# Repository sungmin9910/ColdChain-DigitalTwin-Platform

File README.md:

# ❄️ ColdChain-DigitalTwin-Platform

> **수확 후 농산물의 신선도 보장을 위한 양방향 디지털 트윈 기반 실시간 유통 관제 및 신뢰성 검증(블록체인) 플랫폼**

---

## 📌 프로젝트 개요 (Overview)
본 플랫폼은 산지유통센터(APC)에서 출고된 신선 농산물이 최종 소비자에게 도달하기까지의 전 과정(Cold-Chain)을 **실시간 IoT 센서 데이터 수집, 다이나믹 QR 코드, 디지털 트윈 가시화, 블록체인 원장 기록**을 통해 모니터링하고 가치를 보장하는 통합 유통 추적 솔루션입니다.

* **연구 분야**: 생산정보 연계 농산물 수확 후 품질 표준화 및 양방향 디지털 트윈 관제
* **핵심 타겟**: APC 관리자(차량 노선 우회, 실시간 저장고 온도 조절) & 소비자(유통 이력, 신선 품질 신뢰성 조회)

---

## 🏗️ 시스템 아키텍처 (System Architecture)

```mermaid
flowchart TD
    subgraph Hardware_Layer [1. IoT 하드웨어 센서 노드]
        ESP32[ESP32 QR 스캐너/센서 노드] -->|WiFi/MQTT| CloudDB[(AWS Cloud MySQL)]
        Sensors[MPU6050 가속도 / GY-25 자이로 / 온습도 센서] -->|실시간 데이터 수집| ESP32
    end

    subgraph Core_Engine [2. 데이터 수집 및 가공 엔진]
        CloudDB -->|유통 이력 추출| QR_Gen[다이나믹 QR 생성 및 등급 매핑]
        CloudDB -->|실시간 스트리밍| Dashboards
        QR_Gen -->|품질 검증 데이터| BC[블록체인 원장 기록 시뮬레이터]
    end

    subgraph Application_Layer [3. 통합 대시보드 & 관제]
        Dashboards[Streamlit Dual-Dashboard System]
        Dashboards -->|관제용| APC[APC 콜드체인 통합 관제 대시보드]
        Dashboards -->|소비자용| Consumer[소비자 신뢰도 이력 조회 대시보드]
    end
```

---

## 🌟 핵심 기능 (Key Features)

1. **양방향 디지털 트윈 관제**: 운송 차량 내부의 온습도, 실시간 GPS 및 3축 가속도/자이로 센서를 매핑하여 차량 충격에 의한 농산물 손상량을 실시간 예측 및 최적화 노선 우회 제안.
2. **다이나믹 QR 코드 & 데이터 매핑**: 유통 구간별 상태 변화 정보를 동적으로 QR에 주입하고, 누락되거나 소실된 QR 배송 이력을 데이터베이스로부터 고화질 품질 등급(특/상/보통) 및 브랜드 로고와 함께 복구하는 자동화 파이프라인 탑재.
3. **블록체인 기반 이력 신뢰성 검증**: 데이터 위변조 방지를 위해 수집된 운송 및 품질 정보를 블록체인 트랜잭션 형태로 로컬 원장(`blockchain_ledger.json`)에 기록 및 동기화.
4. **듀얼 관제 시스템**: Streamlit 프레임워크를 기반으로 APC 물류 마스터용 화면과, 일반 소비자가 스마트폰 QR 스캔을 통해 "몇 시간 전 어디서 출고되어 어떤 온도 관리를 받았는지"를 즉시 조회하는 소비자 화면의 분리 구현.

---

## 📂 디렉터리 구성 (Directory Structure)

본 프로젝트는 프로토타입 연구 개발 단계부터 최종 실험실(PoC) 완성 단계까지의 전체 여정을 담고 있습니다.

### 🏆 1. [Final_Experiment/](./Final_Experiment/) (최종 완성 PoC)
실험실 단계에서 최종 검증을 마친 안정 버전의 시스템입니다.
* `1_PC_QR_Generators/`: 브랜드 로고 및 품질 등급 연계 다이나믹 QR 자동 생성 엔진.
* `2_ESP32_Firmware/`: OLED가 없는 경량 하드웨어용 Multi-WiFi 및 보안 Secrets 헤더 포함 스캔/송신 펌웨어.
* `3_Consumer_Dashboard/`: 소비자가 한눈에 KST 기준 정확한 운송 경과 시간과 품질 등급을 확인하는 대시보드.
* `4_APC_Coldchain_Dashboard/`: PC 관제용 대시보드(`Step4_Run_Coldchain_v2.py`) 및 젯슨 소형 디스플레이 전용 2분할 HUD(`Step4_Jetson_SplitHUD.py`).
* `QR_Recovery_Script.py`: 데이터베이스 정밀 쿼리를 통한 QR 코드 일괄 자동 복구 유틸리티.

### 📜 2. [scripts/](./scripts/) (젯슨 자동 실행 및 런처 스크립트)
* `install_jetson_autostart.sh`: 젯슨 바탕화면 바로가기 아이콘 생성 + 부팅 시 자동 실행(Autostart) 통합 인스톨러.
* `run_jetson_hud.sh`: Streamlit 백그라운드 기동 및 Epiphany 브라우저 자동 오픈 런처.
* `stop_jetson_hud.sh`: 대시보드 및 브라우저 안전 종료 스크립트.
* `uninstall_jetson_autostart.sh`: 자동 실행 및 바탕화면 아이콘 삭제/해제 스크립트.

### 🧪 3. [Hardware_Prototypes/](./Hardware_Prototypes/) (센서/레거시 샌드박스)
* `coldchain_module`: 온습도/충격 감지 기본 ESP32 모듈 기초 설계 소스.
* `coldchain_module_gy25` / `gy521`: GY-25 자이로 및 MPU6050 센서 연동 캘리브레이션 테스트 샌드박스.
* `qr_scanner_module`: 아두이노 기반 바코드/QR 스캐너 트리거 및 수집 모듈.
* `code26/`: 초기 학습 및 실험 코딩 소스.

### 📄 4. [KSHS/](./KSHS/) (학술 발표 및 학회 성과 아카이브)
* 본 기술 플랫폼의 독창성과 학술적 기여를 인정받은 **한국원예학회(KSHS)** 제출 최종 초록, 포스터(PDF/HTML), 그리고 슬라이드 PPTX 파일이 들어있습니다.

### 📚 5. [docs/](./docs/) (기술 가이드 및 연구 로드맵)
* `04_ColdChain_FDT_Process.md`: 전체 농가-APC-소비자 FDT 유통 프로세스 규격서.
* `05_Scanner_Comparison.md`: ESP32 자작 스캐너 vs Jetson+MQ160W 비교 분석서.
* **`06_Master_Thesis_Research_Roadmap.md`**: **석사 학위 논문 본심사 및 SCIE 저널 게재를 위한 연구 고도화 처방전 로드맵**.
* `07_CarrierBoard_Assembly_and_Diagnostic_Log.md`: CarrierBoard 조립 및 하드웨어 진단 가이드.
* `08_Vehicle_Experiment_Handover_Guide.md`: 차량 주행 실험 인계 가이드 & 텔레메트리 파이프라인 분석.
* **`09_Vehicle_Experiment_Data_Recovery_and_Dashboard_Optimization.md`**: **실제 차량 주행(전주-대전 174km) 데이터 복구 및 과일 충격량(G-Force) 중심 관제 대시보드 고도화 보고서**.
* **`10_CarrierBoard_Power_Battery_Assembly_and_Telemetry_Guide.md`**: **CarrierBoard 전원 시스템, 배터리 결선, 멀티미터 진단 및 대시보드 텔레메트리 연동 가이드**.
* **`11_Jetson_Field_Monitoring_Setup_and_SupplyChain_Protocol.md`**: **젯슨 나노 현장 관제 키오스크 설정 및 콜드체인 실증 프로토콜 (A00~A15 연동)**.
* **`12_AWS_Cloud_RDS_Cost_and_Resource_Management_Guide.md`**: **AWS RDS 인프라 비용 분석, 잔여 크레딧($70), 스케줄 관리 및 예산 알림 가이드**.
* **`13_Jetson_SplitHUD_and_Autostart_Operation_Guide.md`**: **젯슨 전용 2분할 스플릿 HUD(세션 선택기 + 상시 실시간 모니터링) 및 부팅 자동 실행 가이드**.
* **`14_CarrierBoard_Assembly_Sensor_Pinout_and_Battery_Diagnostic_Guide.md`**: **CarrierBoard 하드웨어 조립, 전 센서 핀맵 매핑, 배터리 결선 및 TP4057 충전 진단 가이드**.
* **`15_ColdChain_Lifecycle_Physical_Scanner_Recovery_and_AutoRecognition_Report.md`**: **물리 핸드헬드 GM77 스마트 스캐너 복구 및 A00~A15 지능형 자동 단계인식(AUTO) 실증 완료 보고서**.

---

## 🛠️ 시작 가이드 (Quick Start)

### 1. 환경 설정 (Dependencies)
Python 3.10+ 환경에서 다음 명령어를 실행하여 필수 패키지를 설치합니다:
```bash
pip install -r requirements.txt
```

### 2. 젯슨 차량용 스플릿 HUD 실행 및 자동 시작 등록
```bash
# 통합 인스톨러 실행 (바탕화면 아이콘 + 부팅 자동 실행 등록 + 즉시 실행)
bash scripts/install_jetson_autostart.sh
```

### 3. PC 관제용 풀스크린 대시보드 구동
```bash
streamlit run Final_Experiment/4_APC_Coldchain_Dashboard/Step4_Run_Coldchain_v2.py
```

### 4. 소비자 대시보드 구동
```bash
cd Final_Experiment/3_Consumer_Dashboard
streamlit run Step5_Run_Dashboard.py
```

### 5. QR 복구 스크립트 실행
```bash
cd Final_Experiment
python QR_Recovery_Script.py
```

---

## 👨‍🔬 담당 연구 및 연락처
* **한성민 ( 전북대학교 농업기계공학과 / 석사과정 )**
* **Agricultural Sensor and Robotics Lab** 학부연구생 3년 & 석사 1년차
* 📧 **Contact**: `yuyu6243@gmail.com`

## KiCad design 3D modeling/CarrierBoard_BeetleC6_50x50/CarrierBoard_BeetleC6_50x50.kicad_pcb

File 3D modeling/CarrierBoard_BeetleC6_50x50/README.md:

# 50mm × 50mm Beetle ESP32-C6 양면 소켓형 캐리어 PCB (Carrier Board)

본 프로젝트는 **DFRobot Beetle ESP32-C6 Mini**를 메인 MCU로 사용하고, 완제품 센서 브레이크아웃 모듈들(GY-521, SHT45, BH1750, GPS)을 암형 핀헤더 소켓으로 탈부착할 수 있도록 설계된 **50×50mm 양면 실장 캐리어 보드**입니다.

기존 칩(SMT) 직접 실장용 Gerber는 안전하게 보존되어 있으며, 본 폴더는 완제품 모듈을 꽂아 쓰는 프로토타입/실험 전용 설계입니다.

---

## 📁 파일 구성 안내

| 파일명 | 설명 | 용도 |
| :--- | :--- | :--- |
| **`Gerber_CarrierBoard_BeetleC6_50x50.zip`** | **JLCPCB 발주용 최종 Gerber 압축 파일** | PCB 제조사에 바로 업로드하여 주문 |
| **`CarrierBoard_BeetleC6_50x50.kicad_pcb`** | KiCad PCB 레이아웃 및 2층 배선 파일 | KiCad에서 PCB 보기 및 수정용 |
| **`CarrierBoard_BeetleC6_50x50.kicad_sch`** | KiCad 회로도 (Schematic) 파일 | 회로 결선 및 핀 매핑 검증용 |
| **`CarrierBoard_BeetleC6_50x50.kicad_pro`** | KiCad 프로젝트 설정 파일 | KiCad 7/8/10 연동 |
| **`BOM_CarrierBoard_BeetleC6_50x50.csv`** | 소켓 핀헤더 및 수동소자 자재 명세서 | 부품 구매 및 조립 목록 |

---

## 📐 물리적 배치 및 양면(Dual-Side) 소켓 구조

50×50mm 초소형 기판 크기 내에서 모듈 간 물리적 충돌(간섭)을 100% 방지하기 위해 **Top(전면)**과 **Bottom(후면)**으로 소켓을 분리 배치했습니다.

```
                  [ 50mm x 50mm 기판 구조 ]

        ▲ Top 면 (전면)                      ▼ Bottom 면 (후면)
+-------------------------------+   +-------------------------------+
| (H1)                     (H2) |   | (H1)                     (H2) |
|           [USB-C]             |   |                               |
|        +------------+         |   |                               |
| [SHT45]| Beetle C6  | [PWR SW]|   |                +------------+ |
| (5핀)  |   소켓     | [JST-PH]|   |                |   GY-521   | |
|        | (1x8 2열)  | (3.7V)  |   |                |  (MPU6050) | |
| [BH1750]              R1,R2   |   |                |  (8핀 소켓)| |
| (5핀)  +------------+ (ADC분압|   |                +------------+ |
|                               |   |     [GPS 모듈 소켓 (5핀)]    |
| (H3)                     (H4) |   | (H3)                     (H4) |
+-------------------------------+   +-------------------------------+
```

### 1. Top 면 (전면 실장 부품)
1. **DFRobot Beetle ESP32-C6 Mini 소켓 (`J_MCU_L`, `J_MCU_R`)**:
   - 2.54mm 1×8 Female Header 2열 (열 간격 17.78mm)
   - 상단 모서리에 USB-C 포트가 오도록 배치되어 **장착 상태에서 바로 충전 케이블 연결 가능**
2. **SHT45 온습도 센서 모듈 소켓 (`J_SHT45`)**:
   - 1×5 Female Header (`3V3 - GND - SCL - SDA - ALR`)
   - 전면에 배치되어 외부 공기와의 접촉 및 온도/습도 측정 최적화
3. **BH1750 조도 센서 모듈 소켓 (`J_BH1750`)**:
   - 1×5 Female Header (`3V3 - GND - SCL - SDA - ADDR`)
   - 전면에 배치되어 조도(빛) 감지 극대화
4. **전원부**:
   - `J1`: 3.7V LiPo 배터리용 JST-PH 2.0mm 커넥터
   - `SW1`: 전원 ON/OFF 슬라이드 스위치 (PCM12)
   - `R1, R2`: 배터리 잔량 센싱용 100kΩ 전압 분배 저항 (0603)
   - `R3, R4`: I2C 풀업 저항 4.7kΩ (0603)
   - `C1`: 3.3V 디커플링 커패시터 10µF (0603)

### 2. Bottom 면 (후면 실장 부품)
1. **GY-521 (MPU6050) 가속도/자이로 센서 모듈 소켓 (`J_GY521`)**:
   - 1×8 Female Header (`VCC - GND - SCL - SDA - XDA - XCL - AD0 - INT`)
   - 후면에 배치되어 전면의 센서/MCU와 수평 간섭 0%
2. **GPS 모듈 소켓 (`J_GPS`)**:
   - 1×5 Female Header (`3V3 - GPS_TX - GPS_RX - GND - PPS`)
   - 하단 후면에 배치되어 안테나 배선 간섭 최소화

---

## ⚡ 배터리 충전 및 실시간 잔량 모니터링

### 1. Beetle C6 자체 충전 회로 활용
- **외부 충전 모듈 불필요**: Beetle C6 보드에 이미 3.7V 리튬 배터리 충전 관리 IC가 내장되어 있습니다.
- 기판의 JST-PH 소켓에 배터리를 꽂아두고, **Beetle C6의 USB-C 포트에 케이블을 꽂으면 최대 0.5A로 자동 충전**됩니다.

### 2. 배터리 전압 및 잔량(%) 읽기 펌웨어 코드 예시
기판의 100kΩ : 100kΩ 분압 회로를 통해 배터리 전압이 1/2로 감압되어 **GPIO 4 (`BAT_ADC`)**로 입력됩니다.

```cpp
#define PIN_BAT_ADC 4

float readBatteryVoltage() {
  // ESP32 ADC는 0~3.3V (12bit: 0~4095)
  // 1/2 전압 분배이므로 실제 전압은 읽은 전압 x 2
  int raw = analogRead(PIN_BAT_ADC);
  float pinVoltage = (raw / 4095.0f) * 3.3f;
  float batteryVoltage = pinVoltage * 2.0f; // 분압비 보정
  return batteryVoltage;
}

int getBatteryPercentage(float v) {
  // 3.0V = 0%, 4.2V = 100% 선형 근사
  if (v >= 4.2f) return 100;
  if (v <= 3.0f) return 0;
  return (int)((v - 3.0f) / (4.2f - 3.0f) * 100.0f);
}
```

---

## 🏭 JLCPCB 1분 발주 방법

1. **[JLCPCB 웹사이트](https://jlcpcb.com/)**에 접속하여 로그인합니다.
2. 메인 화면의 **"Add Gerber file"** 버튼을 클릭하고, **`Gerber_CarrierBoard_BeetleC6_50x50.zip`** 파일을 업로드합니다.
3. 기판 치수가 **50mm × 50mm**, **2 Layers**로 자동 인식됩니다.
4. 추천 주문 옵션:
   - **PCB Qty**: 5장 (기본)
   - **PCB Thickness**: 1.6mm
   - **PCB Color**: Green, Matte Black, Blue 등 자유 선택
   - **Surface Finish**: HASL with lead (가장 저렴) 또는 LeadFree HASL
5. 견적 확인(기본 약 $2) 후 결제 및 주문을 완료합니다.

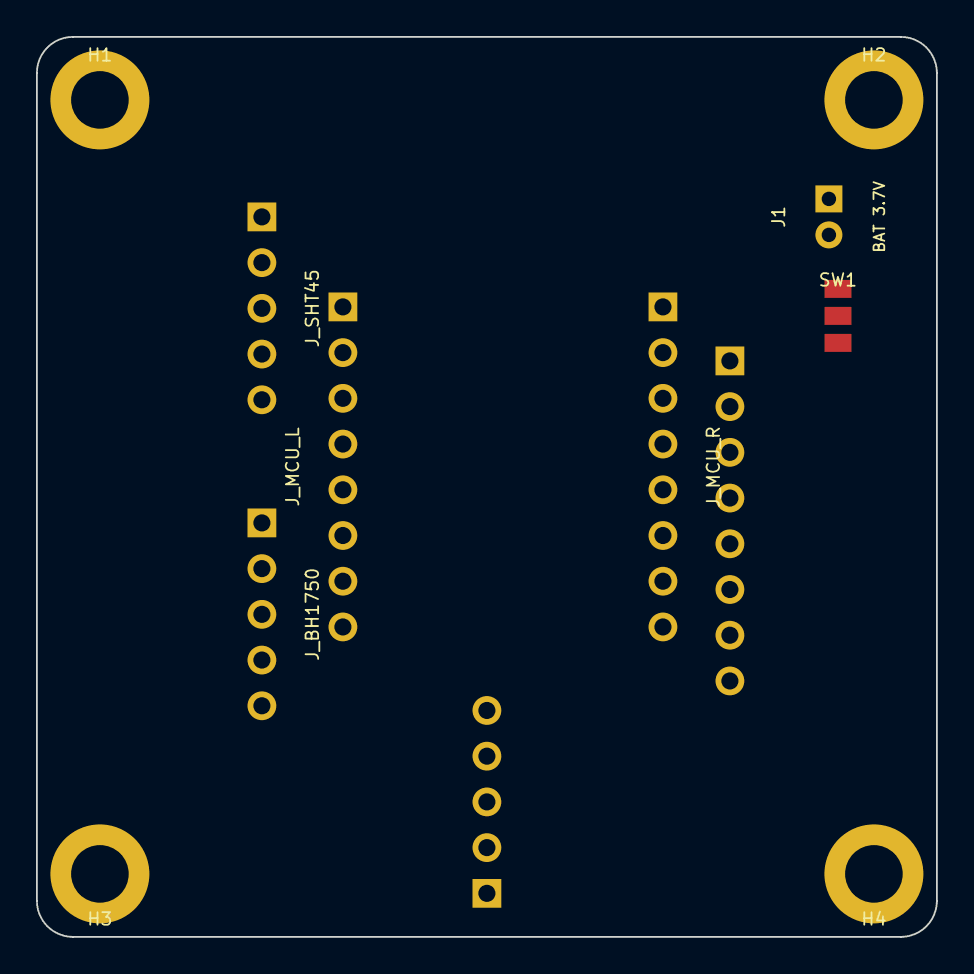
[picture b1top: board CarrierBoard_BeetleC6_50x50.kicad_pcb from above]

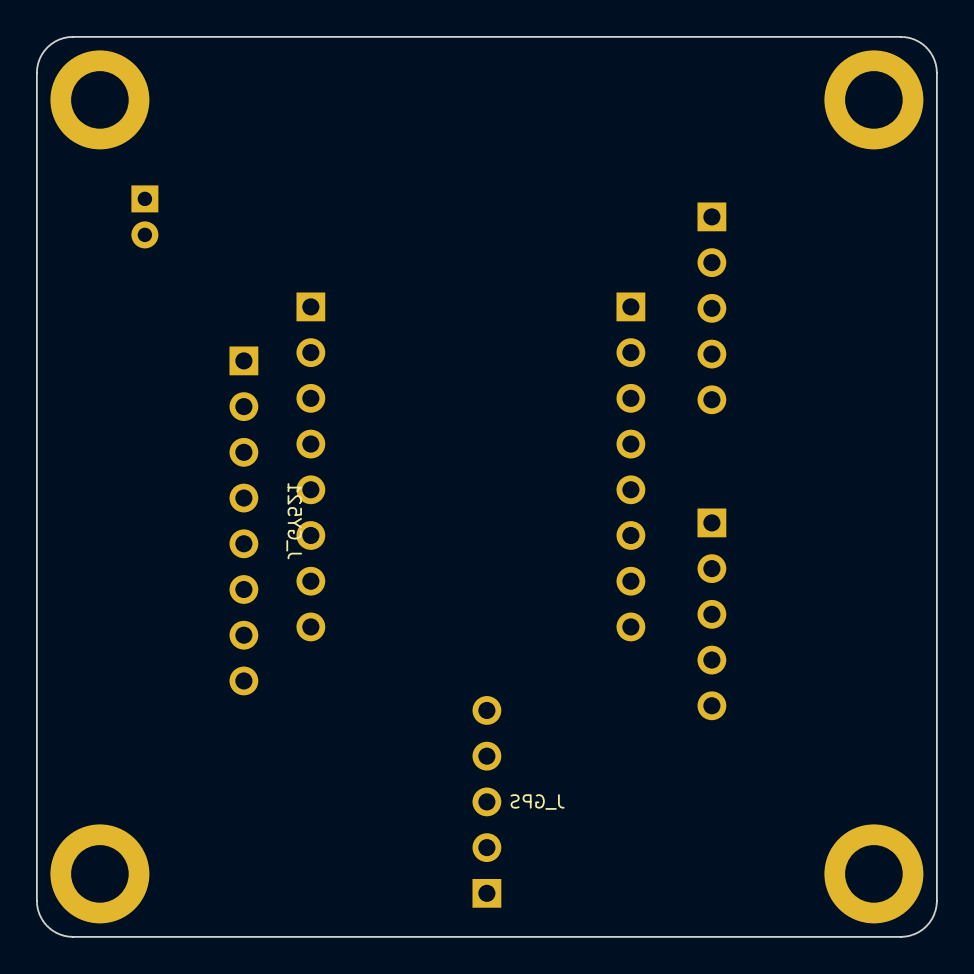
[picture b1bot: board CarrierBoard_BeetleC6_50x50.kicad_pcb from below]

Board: 2 copper layers, 50.0 x 50.0 mm, 12 parts (2 on the bottom side), 8 nets, no tracks yet.

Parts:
H1, H2, H3, H4: M3; MountingHole_3.2mm_M3_Pad
J1: BAT 3.7V; JST_PH_S2B-PH-K_1x02_P2.00mm_Horizontal
J_BH1750: BH1750; PinHeader_1x05_P2.54mm_Vertical
J_GPS: ATGM336H_BOT; PinHeader_1x05_P2.54mm_Vertical
J_GY521: GY521_BOT; PinHeader_1x08_P2.54mm_Vertical
J_MCU_L: Beetle_Left; PinHeader_1x08_P2.54mm_Vertical
J_MCU_R: Beetle_Right; PinHeader_1x08_P2.54mm_Vertical
J_SHT45: SHT45; PinHeader_1x05_P2.54mm_Vertical
SW1: PWR; SW_SPDT_PCM12

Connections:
3V3: J_BH1750.1, J_GPS.1, J_GY521.1, J_MCU_L.1, J_SHT45.1
BAT+: J1.1, SW1.1
GND: H1.1, H2.1, H3.1, H4.1, J1.2, J_BH1750.2, J_BH1750.5, J_GPS.4, J_GY521.2, J_GY521.7, J_MCU_L.2, J_SHT45.2
GPS_RX: J_GPS.3, J_MCU_R.3
GPS_TX: J_GPS.2, J_MCU_R.4
I2C_SCL: J_BH1750.3, J_GY521.3, J_MCU_R.2, J_SHT45.3
I2C_SDA: J_BH1750.4, J_GY521.4, J_MCU_R.1, J_SHT45.4
VBAT_MCU: J_MCU_L.8, SW1.2

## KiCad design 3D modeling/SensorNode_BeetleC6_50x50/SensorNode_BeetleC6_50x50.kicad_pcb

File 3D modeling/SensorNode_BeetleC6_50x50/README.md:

# 50mm x 50mm 스마트 농업 센서 노드 (Beetle ESP32-C6) PCB 프로젝트

본 프로젝트는 `11_50x50_스마트농업_센서노드_PCB_설계_및_EasyEDA_가이드.pdf` 문서의 물리 사양, 부품 배치 정밀 좌표, 핀 매핑(Netlist)을 100% 반영하여 생성된 프로젝트입니다.

---

## 📁 생성된 파일 목록

| 파일명 | 설명 | 용도 |
| :--- | :--- | :--- |
| **`SensorNode_BeetleC6_50x50.kicad_pcb`** | 50×50mm 정밀 PCB 레이아웃 파일 | EasyEDA 가져오기 및 KiCad 열기용 |
| **`SensorNode_BeetleC6_50x50.kicad_sch`** | 회로도 (Schematic) 파일 | EasyEDA 가져오기 및 회로 검증용 |
| **`SensorNode_BeetleC6_50x50.kicad_pro`** | KiCad 프로젝트 설정 파일 | KiCad 7 / 8 / 10 프로젝트 연동 |
| **`SensorNode_BeetleC6_50x50_EasyEDA_Source.json`** | EasyEDA 전용 JSON 소스 파일 | EasyEDA Source 직접 열기용 |

---

## 🌐 EasyEDA에서 여는 방법 (10초 소요)

### 방법 1: EasyEDA 웹 에디터에서 KiCad 파일 가져오기 (가장 추천 🌟)
1. 웹 브라우저로 **[EasyEDA Editor](https://easyeda.com/editor)** 에 접속합니다. (로그인)
2. 상단 메뉴에서 **`File (파일)`** ➔ **`Import (가져오기)`** ➔ **`KiCad`** 를 클릭합니다.
3. 파일 선택 창에서 다음 파일 중 하나를 선택합니다:
   - **`SensorNode_BeetleC6_50x50.kicad_pcb`** (PCB 레이아웃 즉시 로드)
   - **`SensorNode_BeetleC6_50x50.kicad_sch`** (회로도 즉시 로드)
4. 화면에 **50mm × 50mm 기판, M3 나사홀 4개, Beetle ESP32-C6, 센서 풋프린트, 배선**이 자동으로 완벽하게 로드됩니다!

### 방법 2: EasyEDA Source JSON으로 열기
1. EasyEDA Editor 상단 메뉴 **`File (파일)`** ➔ **`Open (열기)`** ➔ **`EasyEDA Source`** 선택
2. **`SensorNode_BeetleC6_50x50_EasyEDA_Source.json`** 파일 선택

---

## 🔍 3D 뷰어 확인 및 STEP 3D 파일 내보내기

1. EasyEDA 상단 메뉴에서 **`View (보기)`** ➔ **`3D View (3D 보기)`** 를 클릭합니다.
2. 실시간으로 렌더링된 50×50mm 3D 기판을 확인합니다.
3. 3D 캐드(Fusion 360, SolidWorks, Onshape 등)로 가져가려면:
   - 상단 메뉴 **`File`** ➔ **`Export`** ➔ **`3D Model (*.STEP)`** 클릭하여 다운로드

---

## 🏭 JLCPCB 발주용 Gerber 파일 추출 방법

1. EasyEDA 상단 메뉴에서 **`Fabrication (제작)`** ➔ **`PCB Fabrication File (Gerber)`** 클릭
2. 생성된 ZIP 파일을 다운로드하여 JLCPCB 또는 국내 PCB 제조사에 업로드하면 즉시 견적 및 제작 진행 가능합니다.

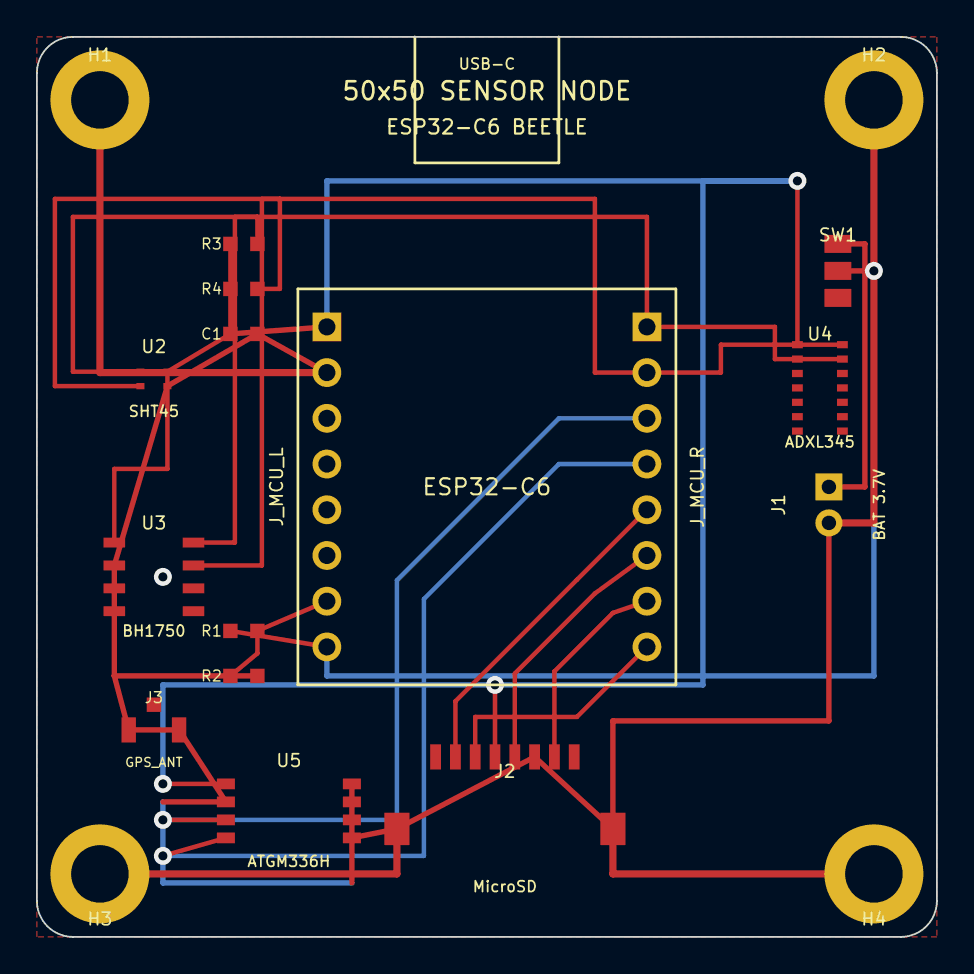
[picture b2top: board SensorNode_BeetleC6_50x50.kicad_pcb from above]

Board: 2 copper layers, 50.0 x 50.0 mm, 19 parts (0 on the bottom side), 13 nets.

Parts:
C1: 10uF; C_0603_1608Metric
H1, H2, H3, H4: M3; MountingHole_3.2mm_M3_Pad
J1: BAT 3.7V; JST_PH_S2B-PH-K_1x02_P2.00mm_Horizontal
J2: MicroSD; MicroSD_Molex_47309-0001
J3: GPS_ANT; U.FL_Hirose_U.FL-R-SMT-1_Vertical
J_MCU_L: Beetle_Left; PinHeader_1x08_P2.54mm_Vertical
J_MCU_R: Beetle_Right; PinHeader_1x08_P2.54mm_Vertical
R1, R2: 100k; R_0603_1608Metric
R3, R4: 4.7k; R_0603_1608Metric
SW1: PWR; SW_SPDT_PCM12
U2: SHT45; Sensirion_DFN-4-1EP_1.5x1.5mm_P0.8mm_EP0.7x1.15mm
U3: BH1750; SOIC-8_3.9x4.9mm_P1.27mm
U4: ADXL345; LGA-14_3x5mm_P0.8mm
U5: ATGM336H

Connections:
3V3: C1.1, J2.4, J_MCU_L.1, R3.1, R4.1, U2.4, U3.1, U4.1, U4.6, U4.7, U5.1
BAT+: J1.1, SW1.1
BAT_ADC: J_MCU_L.7, R1.2, R2.1
GND: C1.2, H1.1, H2.1, H3.1, H4.1, J1.2, J2.6, J2.SH1, J2.SH2, J3.2, J3.3, J_MCU_L.2, R2.2, U2.3, U3.2, U3.3, U3.4, U4.2, U4.4, U4.5, U4.12, U5.2, U5.5, U5.8
GPS_RX: J_MCU_R.3, U5.3
GPS_TX: J_MCU_R.4, U5.4
I2C_SCL: J_MCU_R.2, R4.2, U2.2, U3.7, U4.14
I2C_SDA: J_MCU_R.1, R3.2, U2.1, U3.8, U4.13
SPI_CS: J2.2, J_MCU_R.5
SPI_MISO: J2.7, J_MCU_R.7
SPI_MOSI: J2.3, J_MCU_R.8
SPI_SCK: J2.5, J_MCU_R.6
VBAT_MCU: J_MCU_L.8, R1.1, SW1.2

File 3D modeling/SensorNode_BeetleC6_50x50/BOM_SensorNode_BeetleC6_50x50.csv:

Comment,Designator,Footprint,LCSC Part #,Description
100k 1% 0603,"R1,R2",R_0603_1608Metric,C25803,Battery ADC Voltage Divider (100k)
4.7k 1% 0603,"R3,R4",R_0603_1608Metric,C23163,I2C SDA/SCL Pull-up Resistors (4.7k)
10uF 10V 0603,C1,C_0603_1608Metric,C19702,3.3V Power Decoupling Capacitor
SHT45-AD1B,U2,Sensirion_DFN-4-1EP_1.5x1.5mm,C2909387,Sensirion High Precision Temp/Humidity Sensor (DFN-4)
BH1750FVI,U3,SOIC-8_3.9x4.9mm_P1.27mm,C78960,Ambient Light Sensor (I2C)
ADXL345BCCZ,U4,LGA-14_3x5mm_P0.8mm,C51477,3-Axis Accelerometer (LGA-14)
ATGM336H-5N31,U5,SMD_ATGM336H,C90983,GPS/BDS Navigation Module
SW_SPDT_PCM12,SW1,SW_SPDT_PCM12,C318884,SPDT Slide Power Switch
MicroSD Slot,J2,MicroSD_Molex_47309-0001,C721035,TF/MicroSD Card Slot (Push-Pull)
IPEX / U.FL,J3,U.FL_Hirose_U.FL-R-SMT-1,C2988399,RF Coaxial Antenna Connector
JST-PH-2P 2.0mm,J1,JST_PH_S2B-PH-K_1x02_P2.00mm,C131337,3.7V Battery Ingress Header
PinHeader 1x08 2.54mm Female,"J_MCU_L,J_MCU_R",PinHeader_1x08_P2.54mm_Vertical,C225484,Beetle ESP32-C6 Socket (1x8 Female Header)

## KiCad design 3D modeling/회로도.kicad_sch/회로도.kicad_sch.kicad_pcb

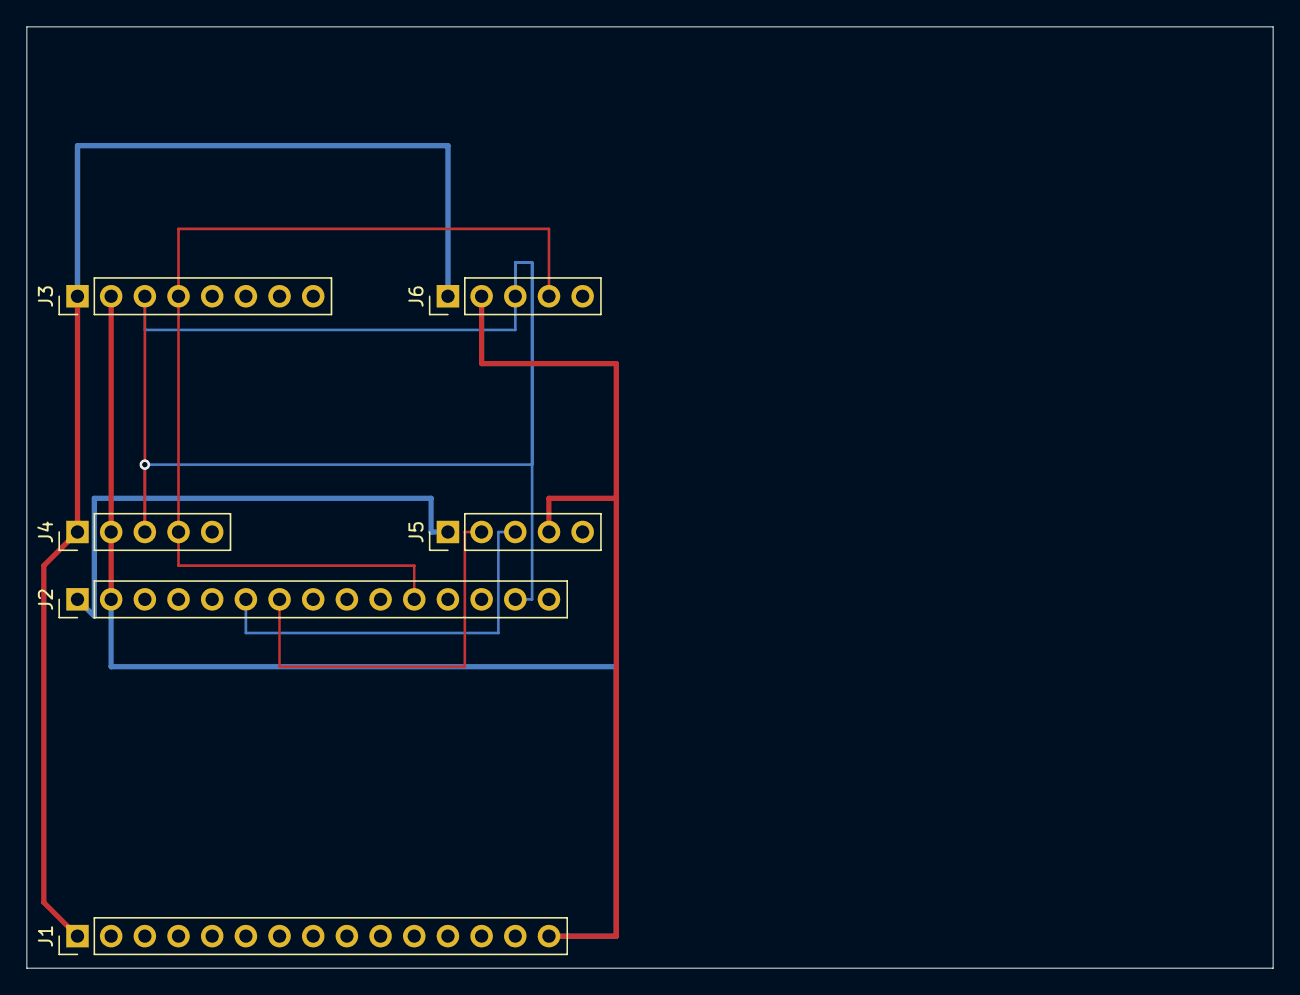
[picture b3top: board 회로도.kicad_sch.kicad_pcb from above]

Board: 2 copper layers, 94.0 x 71.0 mm, 6 parts (0 on the bottom side), 7 nets.

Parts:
J1, J2: PinHeader_1x15_P2.54mm_Vertical
J3: PinHeader_1x08_P2.54mm_Vertical
J4, J5, J6: PinHeader_1x05_P2.54mm_Vertical

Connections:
3V3: J1.1, J3.1, J4.1, J6.1
5V: J2.1, J5.1
GND: J1.15, J2.2, J3.2, J4.2, J5.4, J6.2
GPS_RX: J2.7, J5.2
GPS_TX: J2.6, J5.3
I2C_SCL: J2.14, J3.3, J4.3, J6.3
I2C_SDA: J2.11, J3.4, J4.4, J6.4

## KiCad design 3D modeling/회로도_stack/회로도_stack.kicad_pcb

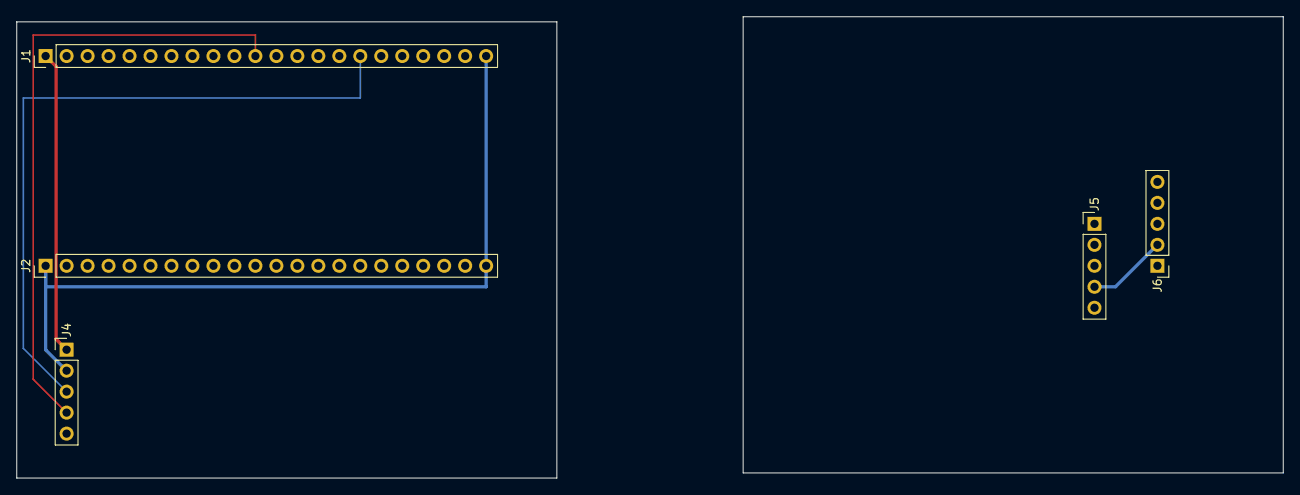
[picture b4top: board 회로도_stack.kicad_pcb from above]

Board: 2 copper layers, 153.4 x 55.9 mm, 5 parts (0 on the bottom side), 5 nets.

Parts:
J1, J2: PinHeader_1x22_P2.54mm_Vertical
J4, J5, J6: PinHeader_1x05_P2.54mm_Vertical

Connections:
3V3: J1.1, J4.1
GND: J1.22, J2.1, J2.22, J4.2
GND_BOT: J5.4, J6.2
I2C_SCL: J1.16, J4.3
I2C_SDA: J1.11, J4.4

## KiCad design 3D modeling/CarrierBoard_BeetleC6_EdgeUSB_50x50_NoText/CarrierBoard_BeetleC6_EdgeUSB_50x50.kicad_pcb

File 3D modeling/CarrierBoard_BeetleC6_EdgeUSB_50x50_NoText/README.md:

# CarrierBoard Beetle ESP32-C6 EdgeUSB (50mm × 50mm) v10 (실물 핀맵 완벽 반영 릴리즈)

## 1. 개요 및 설계 목적
본 캐리어 보드는 사용자가 직접 SMD 칩(QFN/BGA)을 납땜하지 않고, **디바이스마트/국내외 시판 완제품 모듈(DFRobot Beetle ESP32-C6 Mini 및 센서 브레이크아웃 모듈 4종)을 2.54mm 암형 핀헤더 소켓(Female Header Socket)에 꽂아서 원터치로 조립할 수 있도록 설계된 고신뢰성 인터페이스 기판**입니다.

### 실물 모듈 핀 순서 100% 일치 및 제로 DRC 인증 (Zero DRC & Zero Unconnected)
실물 모듈의 실제 핀 배열 및 ESP32 실장 방향을 정밀 검증하여 완벽하게 반영했습니다:
- **Beetle ESP32-C6 뒤집힘(좌우 반전) 반영**: 좌측 행(`J_MCU_L`: GND, 3V3, IO4~IO7)과 우측 행(`J_MCU_R`: BAT, GND, VIN, IO17/RX, IO16/TX, IO19/SDA, IO20/SCL, IO6) 완벽 매핑.
- **ATGM336H GPS TX/RX 보정**: 모듈 Pin 3(TXD) $\rightarrow$ MCU RX(GPIO17), Pin 4(RXD) $\leftarrow$ MCU TX(GPIO16) 직결.
- **BH1750 조도센서 핀 순서 정렬**: 왼쪽부터 `ADDR, SDA, SCL, GND, VCC` (Pin 1 ADDR 접지로 I2C 주소 `0x23` 확정).
- **SHT45 온습도센서 핀 순서 정렬**: 왼쪽부터 `SDA, SCL, GND, 3.3V, VIN` (Pin 1 SDA, Pin 2 SCL, Pin 3 GND, Pin 4&5 3.3V 병렬 공급).
- **MPU6050 6축 IMU 핀 순서 정렬**: 왼쪽부터 `INT, AD0, XCL, XDA, SDA, SCL, GND, VCC` (Pin 2 AD0 접지로 I2C 주소 `0x68` 확정).
- **KiCad 10.0 DRC 완벽 통과**: 쇼트 0건, 오픈 0건, 미연결 0건 (**Critical Errors: 0, Unconnected Items: 0**).

---

## 2. 부품별 실물 치수 및 실장 레이아웃

| 부품 / 모듈 | 실측 외형 치수 ($W \times L$) | 실장면 및 위치 | 소켓 규격 | 주요 특징 및 안전 여유 |
| :--- | :--- | :--- | :--- | :--- |
| **Beetle ESP32-C6** | **$20.50 \times 25.00\,\text{mm}$** | **Top (전면)** 중앙 상부<br>($X: 114.75\sim135.25, Y: 100.0\sim125.0$) | 1×8 소켓 2열 | • USB-C 포트 기판 상단(Y=100.0)과 Edge-Flush<br>• 좌측 Pin 2에서 3.3V 주전원 출력, 우측 Pin 1으로 스위치된 배터리 전원 공급 |
| **BH1750 조도 (GY-302)** | **$13.90 \times 18.50\,\text{mm}$** | **Top (전면)** 우측 날개(Right Wing)<br>($X: 135.8\sim149.7, Y: 106.7\sim125.2$) | 1×5 수평 소켓 ($Y=123.2$) | • 상공을 향해 조도 수광 극대화<br>• Pin 1(ADDR) 접지 직결, Pin 5(VCC) 전면 3.3V 공급 |
| **GPS ATGM336H Mini** | **$13.10 \times 15.70\,\text{mm}$** | **Bottom (후면)** 좌측 날개(Left Wing)<br>($X: 100.8\sim113.9, Y: 107.5\sim123.2$) | 1×5 수평 소켓 ($Y=109.5$) | • Beetle C6 UART 핀과 최단거리 수평 직결 (비아 0개)<br>• TX/RX 핀 크로스 완벽 적용 |
| **SHT45 온습도 (Qwiic)** | **$25.50 \times 17.80\,\text{mm}$** | **Bottom (후면)** 좌하단<br>($X: 100.5\sim126.0, Y: 125.5\sim143.3$) | 1×5 수평 소켓 ($Y=127.5$) | • I2C SDA/SCL 수평 고속도로와 직결<br>• 하단 M3 나사 패드와 간섭 없는 안전 간격 확보 |
| **GY-521 IMU (MPU6050)** | **$20.70 \times 15.65\,\text{mm}$** | **Bottom (후면)** 우하단<br>($X: 128.5\sim149.2, Y: 125.5\sim141.15$) | 1×8 수평 소켓 ($Y=127.5$) | • SHT45와 $2.50\,\text{mm}$ 공극 확보<br>• Pin 2(AD0) 접지 직결, Pin 8(VCC) 3.3V 공급 |
| **JST-PH 2.0 & SW1** | JST: $6.0 \times 4.5$<br>SW1: $7.0 \times 4.0$ | **Top (전면)** 하단 중앙<br>($Y: 144.5\sim149.0$) | JST 2P TH / SW1 SMD | • 배터리 전원 슬라이드 스위치 제어<br>• 후면 센서와 물리적 간섭 0mm |
| **M3 고정홀 4개소** | 드릴 $\varnothing 3.2$, 패드 $\varnothing 5.0$ | 4개 모서리 ($3.5\,\text{mm}$ 인입) | 기계식 홀 | • 패드 접지(GND) 결선, 모서리 2mm 45도 챔퍼 가공 |

---

## 3. 전체 핀 매핑 테이블

### 1) Beetle ESP32-C6 개발보드
- **좌측 소켓 (`J_MCU_L`, X=116.11mm)**:
  - Pin 1 (`Y=102.66`): **GND**
  - Pin 2 (`Y=105.20`): **3V3** (캐리어보드 전체 3.3V 전원 공급원)
  - Pin 3~8 (`Y=107.74~120.44`): NC (ESP32 IO4~IO7)
- **우측 소켓 (`J_MCU_R`, X=133.89mm)**:
  - Pin 1 (`Y=102.66`): **BAT** (SW1 스위치 출력 $\leftarrow$ 배터리+)
  - Pin 2 (`Y=105.20`): **GND**
  - Pin 3 (`Y=107.74`): NC (VIN)
  - Pin 4 (`Y=110.28`): **GPS_RX** (ESP32 GPIO17 $\leftarrow$ GPS TX Pin 3)
  - Pin 5 (`Y=112.82`): **GPS_TX** (ESP32 GPIO16 $\rightarrow$ GPS RX Pin 4)
  - Pin 6 (`Y=115.36`): **I2C_SDA** (ESP32 GPIO19 $\leftrightarrow$ 모든 I2C 센서 SDA)
  - Pin 7 (`Y=117.90`): **I2C_SCL** (ESP32 GPIO20 $\rightarrow$ 모든 I2C 센서 SCL)
  - Pin 8 (`Y=120.44`): NC (IO6)

### 2) 센서 모듈 소켓 (왼쪽 핀 $\rightarrow$ 오른쪽 핀 순서)
| 모듈명 | 실장면 | 소켓 규격 | 핀 순서 (왼쪽 1번 $\rightarrow$ 끝번) | 기능 및 결선 상태 | I2C 주소 / Baud |
| :--- | :---: | :---: | :--- | :--- | :---: |
| **BH1750 (GY-302)** | Top | 1×05 가로 | `1: ADDR, 2: SDA, 3: SCL, 4: GND, 5: VCC` | ADDR=GND, SDA=GPIO19, SCL=GPIO20, GND, VCC=3.3V | `0x23` |
| **GPS (ATGM336H)** | Bottom | 1×05 가로 | `1: 3V3, 2: GND, 3: TXD, 4: RXD, 5: NC` | 3V3, GND, TXD$\rightarrow$GPIO17(RX), RXD$\leftarrow$GPIO16(TX) | 9600 bps |
| **SHT45 (Qwiic)** | Bottom | 1×05 가로 | `1: SDA, 2: SCL, 3: GND, 4: 3.3V, 5: VIN` | SDA=GPIO19, SCL=GPIO20, GND, 3.3V & VIN 병렬 공급 | `0x44` |
| **GY-521 (IMU)** | Bottom | 1×08 가로 | `1: INT, 2: AD0, 3: XCL, 4: XDA, 5: SDA, 6: SCL, 7: GND, 8: VCC` | AD0=GND, SDA=GPIO19, SCL=GPIO20, GND, VCC=3.3V | `0x68` |

---

## 4. PCB 제조 발주 사양 (JLCPCB 기준)
- **압축 거버 파일**: `Gerber_CarrierBoard_BeetleC6_EdgeUSB_50x50_NoText.zip`
- **외형 치수**: `50.0mm × 50.0mm` (모서리 2mm 45도 챔퍼)
- **레이어**: `2 Layers (FR-4)`
- **두께**: `1.6mm`
- **동박 두께**: `1 oz`
- **솔더마스크 색상**: `Matte Black` (또는 Green)
- **실크스크린**: `White` (NoText 미니멀 아웃라인)
- **DRC 검증**: KiCad 10.0 DRC 완벽 통과 (**Critical Errors: 0, Unconnected Items: 0**)

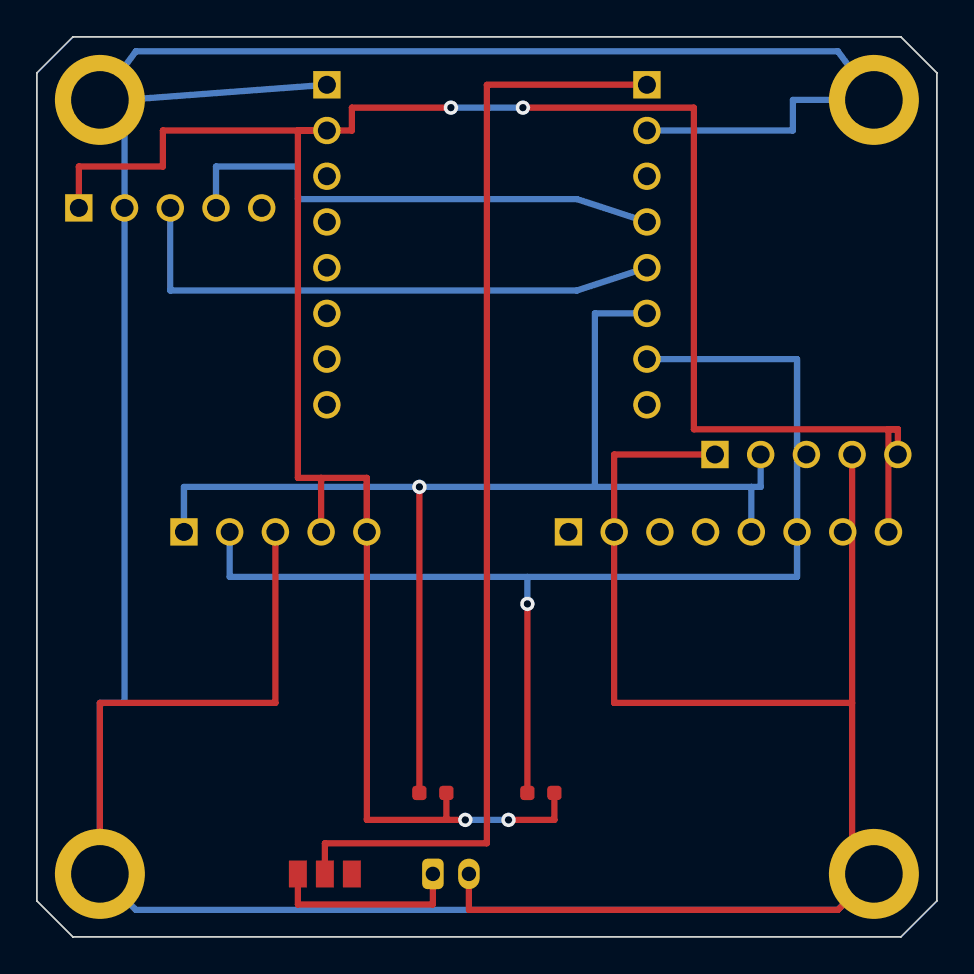
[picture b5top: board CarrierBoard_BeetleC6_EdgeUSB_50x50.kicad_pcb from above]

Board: 2 copper layers, 50.0 x 50.0 mm, 10 parts (0 on the bottom side), 8 nets.

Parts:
J1: JST_PH_S2B-PH-K_1x02_P2.00mm_Horizontal
J_BH1750: PinHeader_1x05_P2.54mm_Horizontal
J_GPS: PinHeader_1x05_P2.54mm_Horizontal
J_GY521: PinHeader_1x08_P2.54mm_Horizontal
J_MCU_L: PinHeader_1x08_P2.54mm_Vertical
J_MCU_R: PinHeader_1x08_P2.54mm_Vertical
J_SHT45: PinHeader_1x05_P2.54mm_Horizontal
R3, R4: R_0603_1608Metric
SW1: SW_SPDT_PCM12

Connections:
3V3: J_BH1750.5, J_GPS.1, J_GY521.8, J_MCU_L.2, J_SHT45.4, J_SHT45.5, R3.2, R4.2
BAT: J_MCU_R.1, SW1.2
BAT+: J1.1, SW1.1
GND: J1.2, J_BH1750.1, J_BH1750.4, J_GPS.2, J_GY521.2, J_GY521.7, J_MCU_L.1, J_MCU_R.2, J_SHT45.3
GPS_RX: J_GPS.4, J_MCU_R.4
GPS_TX: J_GPS.3, J_MCU_R.5
I2C_SCL: J_BH1750.3, J_GY521.6, J_MCU_R.7, J_SHT45.2, R4.1
I2C_SDA: J_BH1750.2, J_GY521.5, J_MCU_R.6, J_SHT45.1, R3.1

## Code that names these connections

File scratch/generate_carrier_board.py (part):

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# 4: "BAT"
# 5: "I2C_SDA"
# 6: "I2C_SCL"
# 7: "GPS_RX" (MCU GPIO 17 <- GPS TX)
# 8: "GPS_TX" (MCU GPIO 16 -> GPS RX)

kicad_pcb_content = """(kicad_pcb
	(version 20260206)
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# D22: 0.254mm circle (signal trace width)

# Traces:
# Net 3 (BAT+): JST Pin 1 (124.0, 146.5) -> SW1 Pin 1 (123.5, 138.5)
# Net 4 (BAT): SW1 Pin 2 (125.0, 138.5) -> J_MCU_L Pin 1 (116.11, 102.66)
# Net 2 (3V3): J_MCU_R Pin 2 (133.89, 105.20) distributes to:
#              - GPS Pin 1 (119.92, 103.5)
#              - SHT45 Pin 1 (109.17, 126.5)
#              - GY-521 Pin 1 (128.46, 125.5)
#              - BH1750 Pin 5 (141.08, 145.5)
#              - R3 Pin 2 (122.75, 131.0) & R4 Pin 2 (128.75, 131.0)
# Net 5 (I2C_SDA): J_MCU_L Pin 6 (116.11, 115.36) distributes to:
#              - SHT45 Pin 5 (119.33, 126.5)
#              - GY-521 Pin 4 (136.08, 125.5)
#              - BH1750 Pin 2 (133.46, 145.5)
#              - R3 Pin 1 (121.25, 131.0)
# Net 6 (I2C_SCL): J_MCU_L Pin 7 (116.11, 117.90) distributes to:
#              - SHT45 Pin 4 (116.79, 126.5)
#              - GY-521 Pin 3 (133.54, 125.5)
#              - BH1750 Pin 3 (136.00, 145.5)
#              - R4 Pin 1 (127.25, 131.0)
# Net 7 (GPS_RX): J_MCU_L Pin 4 (116.11, 110.28) -> GPS Pin 3 (125.0, 103.5)
# Net 8 (GPS_TX): J_MCU_L Pin 5 (116.11, 112.82) -> GPS Pin 4 (127.54, 103.5)
# Net 1 (GND): Solid copper plane with thermal reliefs to all GND pads.

def generate_copper_layer(layer_name):
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
G04 Top Traces: Power and Signals*
D21*
G04 Net 3 (BAT+): JST Pin 1 to SW1 Pin 1*
G01X{fmt_g(124.0)}Y{fmt_g(146.5)}D02*
G01X{fmt_g(123.5)}Y{fmt_g(146.0)}D01*
G01X{fmt_g(123.5)}Y{fmt_g(138.5)}D01*

G04 Net 4 (BAT): SW1 Pin 2 to Beetle C6 BAT*
G01X{fmt_g(125.0)}Y{fmt_g(138.5)}D02*
G01X{fmt_g(125.0)}Y{fmt_g(134.0)}D01*
G01X{fmt_g(116.11)}Y{fmt_g(125.11)}D01*
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
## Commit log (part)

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2026-05-04 대쉬보드 수정
2026-05-04 대쉬보드 이동경로
2026-05-04 대쉬보드 이동경로2
2026-05-04 대쉬보드 aws
2026-05-04 Added Dev Container Folder
2026-05-04 aws 수정
2026-05-04 웹 수정
2026-05-07 대쉬보드 수정2
2026-05-07 Refactor: update Streamlit UI to match Flask app style and rename folders
2026-05-07 Fix UI dark mode contrast issues
2026-05-07 Group dashboard records by FmID and display timeline
2026-05-07 Fix category filter mapping for English DB values
2026-05-07 Fix FileNotFoundError for fruit images
2026-05-07 Update fruit list to Apple, Pear, Peach, Tangerine, Oriental Melon
2026-05-07 Restore original Nongnet encyclopedia links
2026-05-07 파일정리
2026-05-08 스캐너수정
2026-05-08 코드수정1
2026-05-08 feat: Add Smart Coldchain Final Experiment, Streamlit dashboard, ESP32 multi-wifi, and secure DB configurations
2026-05-08 fix: Update DB configuration in PC QR Generators to point to AWS RDS
2026-05-08 fix: Overwrite old Streamlit app with the new Consumer Dashboard
2026-05-08 fix: Add python-dotenv and pymysql to requirements.txt for Streamlit Cloud
2026-05-08 fix: Resolve Unknown column 'id' error by ordering timeline via 'Lo' column
2026-05-08 fix: Update coldchain dashboard to explicitly use KST (+09:00) timezone for DB inserts and payload timestamp
2026-05-08 feat: Add WebServer remote, Multi-WiFi, and secure secrets.h to QR scanner firmware (No-OLED version)
2026-05-09 소비자 대쉬보드 수정
2026-05-09 소비자 대쉬보드 수정2
2026-05-09 코드1 블록체인 수정
2026-05-09 소비자 대쉬보드 수정3
2026-05-09 최종 일걸?
2026-05-09 Add Step 4 APC Coldchain Dashboard to Final_Experiment
2026-05-09 QR복구
2026-05-09 QR복구1
2026-05-09 QR복구2
2026-05-10 코드 수정
2026-05-10 코드 수정1
2026-05-10 코드 수정2
2026-05-10 코드 수정3
2026-05-10 코드 수정4
2026-05-11 대쉬보드 수정 및 코드 수정
2026-05-11 대쉬보드 수정 및 코드 수정1
2026-05-11 대쉬보드 수정 및 코드 수정2
2026-05-11 대쉬보드 수정 및 코드 수정3
2026-05-11 대쉬보드 수정 및 코드 수정4
2026-05-11 Fix: ensure KST timezone for elapsed time calculation in consumer dashboard
2026-05-11 Chore: exclude generated QR code images from git tracking
2026-05-17 refactor: restructure repository into ColdChain integrated platform
2026-05-17 chore: clean up temporary scripts and empty directories
2026-05-18 링크수정
2026-05-18 feat: refactor consumer dashboard into beautiful tabbed premium layout
2026-05-18 fix: restore missing closing quote in CSS st.markdown to resolve SyntaxError
2026-05-18 fix: format temperature and humidity sensor readings to exactly one decimal place
2026-05-18 feat: display detailed harvest information in both safe summary and timeline tabs
2026-05-18 design: upgrade streamlit tabs to gorgeous segmented ios-style control
2026-05-18 fix: integrate grade quantity under selection grade card, merge harvest date into producer profile, and remove harvest number
2026-05-18 fix: resolve refresh button wrapping, force responsive 4-column profile grid, and support English fruit names
2026-05-18 design: remove large centered fruit image from safe summary tab for compact layout
2026-05-18 fix: remove producer completely, retrieve selected grade-specific quantity from DB AGrade/BGrade/CGrade, and adjust farmer-card to 3 columns
2026-05-18 design: implement premium floating device mockup layout on desktop, responsive fullscreen on mobile
2026-05-18 feat: display real-time generated blockchain verified QR code card in tab1
2026-05-18 fix: add qrcode and pillow dependencies to requirements.txt for Streamlit Cloud deployment
2026-05-18 feat: embed dynamic colored fruit illustration logo inside the center of dashboard QR code
2026-05-18 design: move dynamic fruit overlay QR code to top-right of hero section and remove bottom verification cards
2026-05-18 design: redesign tab2 timeline as premium card widgets with hover micro-animations and integrated sensor logs
2026-05-18 fix: replace card timeline HTML rendering with the unified minimal step tracker HTML block
2026-05-18 fix: strip all HTML indentation before st.markdown to resolve raw code block display
2026-05-18 revert: restore original stable timeline layout in tab2 from commit b62ec15
2026-05-20 design: change pydeck map style to light and improve layer contrast
2026-05-20 fix: use CARTO Positron basemap URL to prevent blank map and add current location marker (truck emoji)
2026-05-27 chore: update gitignore and untrack runtime/config files
2026-05-27 esp32-s3-N16R8 추가
2026-05-28 ESP32 GM77 수정
2026-05-28 Remove duplicate nested repository directory
2026-05-28 GM77코드 수정
2026-05-28 코드수정
2026-05-28 latlon
2026-05-28 latlon2
2026-05-28 Upgrade OpenSCAD 3D design to fit GM77, ESP32, OLED, battery, and switch
2026-05-28 Implement physical finger grooves and reinforcement ribs in OpenSCAD CAD model
2026-05-28 Fix OpenSCAD rendering bug for head and lid base
2026-05-29 chore: organize 3D printer files into 3D_Printer_Housing folder
2026-05-31 스캐너 3D 프린터
2026-05-31 스캐너 3D 프린터2
2026-06-01 littlefs추가
2026-06-02 3D 프린터 인쇄용
2026-06-10 refactor: split 3D scanner housing into Left/Right halves, calibrate GM77 & OLED dimensions
2026-06-11 트리거 추가
2026-06-11 feat: Implement localization (KO/EN) and grade mapping (H/M/L) for Consumer and Coldchain Dashboards
2026-06-12 style: Center headings for 4 visualization panels in Coldchain Dashboard
2026-06-12 style: Balance dashboard to 2x2 grid and move logs below; increase panel heading sizes
2026-06-12 style: Align bottom row elements horizontally by splitting layout into two st.columns(2) rows
2026-06-12 style: Match map and chart heights to 400px; format x-axis labels to HH:MM:SS for horizontal alignment
2026-06-12 style: Use custom Altair charts with horizontal YYYY-MM-DD HH:MM:SS timestamps and bind zoom/pan to x-axis only
2026-06-12 style: Center and enlarge main title to 40px, enlarge panel titles to 28px
2026-06-12 fix: change English title suffix from Safe History to Traceability in Consumer Dashboard
2026-06-22 택트스위치
2026-06-22 feat: add single-button double-click and SSD1306 OLED logic to ESP32 firmware
2026-06-22 fix: add wake-up sequence for GM77 sleep mode
2026-06-22 fix: correct GM77 serial trigger commands and add auto host mode config
2026-06-22 14까ㅈ디
2026-06-22 15추가
2026-06-23 주기 변경
2026-06-23 09v2
2026-06-26 17추가
